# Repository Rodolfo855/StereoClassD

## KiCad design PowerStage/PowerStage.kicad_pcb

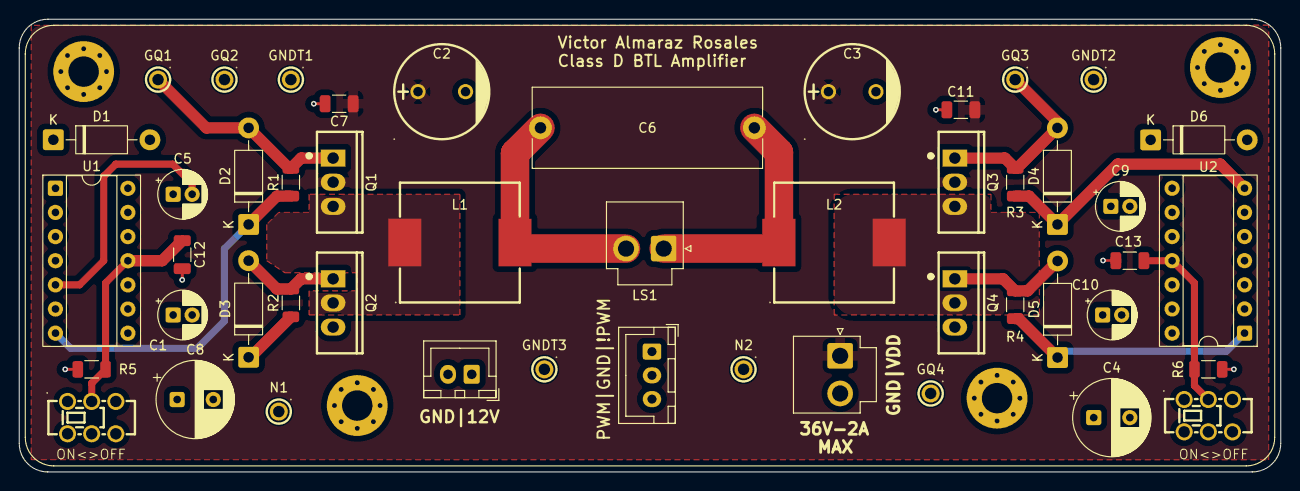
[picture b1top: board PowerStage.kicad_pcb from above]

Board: 4 copper layers, 132.7 x 47.6 mm, 52 parts (0 on the bottom side), 21 nets.

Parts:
C1, C5: C_Polarized_Small; CP_Radial_D5.0mm_P2.00mm
C2, C3: 470uF 16V; C46550425_CAP-TH_BD10_0-P5_00-D0_6-FD-A
C4, C8: 100uF; CP_Radial_D8.0mm_P3.80mm
C6: 680nF; C_Rect_L24.0mm_W8.3mm_P22.50mm_MKT
C7, C11: 100nF; C_1206_3216Metric
C9, C10: 1uF; CP_Radial_D5.0mm_P2.00mm
C12: 100nF 1206; C_1206_3216Metric
C13: 100nF-1206; C_1206_3216Metric
D1, D2, D3, D4, D5, D6: 1N5819; D_DO-41_SOD81_P10.16mm_Horizontal
GNDT1, GNDT2, GNDT3: TestPoint; C5277086_TEST-TH_BD2_54-P1_4_RED
GQ1, GQ2, GQ3, GQ4: TestPoint; C5277086_TEST-TH_BD2_54-P1_4_RED
H1, H2, H3, H4: MountingHole; MountingHole_3.2mm_M3_Pad_Via
J1: Conn_01x02; JST_VH_B2P-VH_1x02_P3.96mm_Vertical
J2: Conn_01x02; JST_XH_B2B-XH-A_1x02_P2.50mm_Vertical
J3: Conn_01x03; JST_XH_B3B-XH-A_1x03_P2.50mm_Vertical
L1, L2: MDA1365-470M; C2847587_IND-SMD_L13_5-W12_6_TMPA1265SP-100MN-D
LS1: 8 Ohms; JST_VH_B2P-VH_1x02_P3.96mm_Vertical
N1, N2: TestPoint; C5277086_TEST-TH_BD2_54-P1_4_RED
Q1, Q2, Q3, Q4: IRFB4227PBF; C2652_TO-220-3_L10_0-W4_5-P2_54-L
R1: R_Small_US; R_1206_3216Metric
R2, R3, R4: 10; R_1206_3216Metric
R5, R6: 10k-1206; R_1206_3216Metric
SW1, SW2: K2-2235D-F1; C108742_SW-TH_K2-2235D-F1
U1, U2: IR2110; DIP-14_W7.62mm_Socket

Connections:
!PWM: J3.1, U1.12 (LIN), U2.10 (HIN)
+12V: C1.1, C4.1, C8.1, C10.1, D1.2 (A), D6.2 (A), J2.1, SW1.1, SW2.1, U1.3 (VCC), U1.9 (VDD), U2.3 (VCC), U2.9 (VDD)
GND: C1.2, C2.2, C3.2, C4.2, C7.2, C8.2, C10.2, C11.2, C12.2, C13.2, GNDT1.1, GNDT2.1, GNDT3.1, J1.2, J2.2, J3.2, Q2.3 (S), Q4.3 (S), R5.2, R6.2, SW1.3, SW2.3, U1.2 (COM), U1.13 (VSS), U2.2 (COM), U2.13 (VSS)
unnamed: C6.1, L2.1, LS1.1
unnamed: C6.2, L1.2, LS1.2
unnamed: C5.1, D1.1 (K), U1.6 (VB)
unnamed: D2.2 (A), GQ1.1, Q1.1 (G), R1.2
unnamed: D2.1 (K), R1.1, U1.7 (HO)
unnamed: D3.2 (A), GQ2.1, Q2.1 (G), R2.2
unnamed: D3.1 (K), R2.1, U1.1 (LO)
unnamed: D4.2 (A), GQ3.1, Q3.1 (G), R3.1
unnamed: D4.1 (K), R3.2, U2.7 (HO)
unnamed: D5.2 (A), GQ4.1, Q4.1 (G), R4.1
unnamed: D5.1 (K), R4.2, U2.1 (LO)
unnamed: C9.1, D6.1 (K), U2.6 (VB)
unnamed: C5.2, L1.1, N1.1, Q1.3 (S), Q2.2 (D), U1.5 (VS)
unnamed: C9.2, L2.2, N2.1, Q3.3 (S), Q4.2 (D), U2.5 (VS)
unnamed: C12.1, R5.1, SW1.2, U1.11 (SD)
unnamed: C13.1, R6.1, SW2.2, U2.11 (SD)
PWM: J3.3, U1.10 (HIN), U2.12 (LIN)
VDC: C2.1, C3.1, C7.1, C11.1, J1.1, Q1.2 (D), Q3.2 (D)

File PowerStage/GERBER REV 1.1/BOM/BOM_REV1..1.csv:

"Reference","Value","DNP","Exclude from BOM","Footprint","LCSC"
"C1","C_Polarized_Small","","","Capacitor_THT:CP_Radial_D5.0mm_P2.00mm","C330941"
"C2","470uF 16V","","","lcsc_footprints:C46550425_CAP-TH_BD10_0-P5_00-D0_6-FD-A","C2837182"
"C3","470uF 16V","","","lcsc_footprints:C46550425_CAP-TH_BD10_0-P5_00-D0_6-FD-A","C2837182"
"C4","100uF","","","Capacitor_THT:CP_Radial_D8.0mm_P3.50mm","C1669449"
"C5","C_Polarized_Small","","","Capacitor_THT:CP_Radial_D5.0mm_P2.00mm","C330941"
"C6","680nF","","Excluded from BOM","Capacitor_THT:C_Rect_L24.0mm_W8.3mm_P22.50mm_MKT",""
"C7","100nF","","","Capacitor_SMD:C_1206_3216Metric","C24497"
"C8","100uF","","","Capacitor_THT:CP_Radial_D8.0mm_P3.50mm","C1669449"
"C9","1uF","","","Capacitor_THT:CP_Radial_D5.0mm_P2.00mm","C330941"
"C10","1uF","","","Capacitor_THT:CP_Radial_D5.0mm_P2.00mm","C330941"
"C11","100nF","","","Capacitor_SMD:C_1206_3216Metric","C24497"
"C12","100nF 1206","","","Capacitor_SMD:C_1206_3216Metric","C24497"
"C13","100nF-1206","","","Capacitor_SMD:C_1206_3216Metric","C24497"
"D1","1N5819","","","Diode_THT:D_DO-41_SOD81_P10.16mm_Horizontal","C16588"
"D2","1N5819","","","Diode_THT:D_DO-41_SOD81_P10.16mm_Horizontal","C16588"
"D3","1N5819","","","Diode_THT:D_DO-41_SOD81_P10.16mm_Horizontal","C16588"
"D4","1N5819","","","Diode_THT:D_DO-41_SOD81_P10.16mm_Horizontal","C16588"
"D5","1N5819","","","Diode_THT:D_DO-41_SOD81_P10.16mm_Horizontal","C16588"
"D6","1N5819","","","Diode_THT:D_DO-41_SOD81_P10.16mm_Horizontal","C16588"
"H1","MountingHole","","Excluded from BOM","MountingHole:MountingHole_3.2mm_M3_Pad_Via",""
"H2","MountingHole","","Excluded from BOM","MountingHole:MountingHole_3.2mm_M3_Pad_Via",""
"H3","MountingHole","","Excluded from BOM","MountingHole:MountingHole_3.2mm_M3_Pad_Via",""
"H4","MountingHole","","Excluded from BOM","MountingHole:MountingHole_3.2mm_M3_Pad_Via",""
"J1","Conn_01x02","","Excluded from BOM","Connector_JST:JST_VH_B2P-VH_1x02_P3.96mm_Vertical",""
"J2","Conn_01x02","","Excluded from BOM","Connector_JST:JST_XH_B2B-XH-A_1x02_P2.50mm_Vertical",""
"J3","Conn_01x03","","Excluded from BOM","Connector_JST:JST_XH_B3B-XH-A_1x03_P2.50mm_Vertical",""
"L1","MDA1365-470M","","","lcsc_footprints:C2847587_IND-SMD_L13_5-W12_6_TMPA1265SP-100MN-D","C2847587"
"L2","MDA1365-470M","","","lcsc_footprints:C2847587_IND-SMD_L13_5-W12_6_TMPA1265SP-100MN-D","C2847587"
"LS1","8 Ohms","","Excluded from BOM","Connector_JST:JST_VH_B2P-VH_1x02_P3.96mm_Vertical",""
"Q1","IRFB4227PBF","","","lcsc_footprints:C2652_TO-220-3_L10_0-W4_5-P2_54-L","C2652"
"Q2","IRFB4227PBF","","","lcsc_footprints:C2652_TO-220-3_L10_0-W4_5-P2_54-L","C2652"
"Q3","IRFB4227PBF","","","lcsc_footprints:C2652_TO-220-3_L10_0-W4_5-P2_54-L","C2652"
"Q4","IRFB4227PBF","","","lcsc_footprints:C2652_TO-220-3_L10_0-W4_5-P2_54-L","C2652"
"R1","R_Small_US","","","Resistor_SMD:R_1206_3216Metric","C17903"
"R2","10","","","Resistor_SMD:R_1206_3216Metric","C17903"
"R3","10","","","Resistor_SMD:R_1206_3216Metric","C17903"
"R4","10","","","Resistor_SMD:R_1206_3216Metric","C17903"
"R5","10k-1206","","","Resistor_SMD:R_1206_3216Metric","C17902"
"R6","10k-1206","","","Resistor_SMD:R_1206_3216Metric","C17902"
"SW1","K2-2235D-F1","","","lcsc_footprints:C108742_SW-TH_K2-2235D-F1","C108742"
"SW2","K2-2235D-F1","","","lcsc_footprints:C108742_SW-TH_K2-2235D-F1","C108742"
"TP1","TestPoint","","","lcsc_footprints:C5277086_TEST-TH_BD2_54-P1_4_RED","C5277086"
"TP2","TestPoint","","","lcsc_footprints:C5277086_TEST-TH_BD2_54-P1_4_RED","C5277086"
"TP3","TestPoint","","","lcsc_footprints:C5277086_TEST-TH_BD2_54-P1_4_RED","C5277086"
"TP4","TestPoint","","","lcsc_footprints:C5277086_TEST-TH_BD2_54-P1_4_RED","C5277086"
"TP5","TestPoint","","","lcsc_footprints:C5277086_TEST-TH_BD2_54-P1_4_RED","C5277086"
"TP6","TestPoint","","","lcsc_footprints:C5277086_TEST-TH_BD2_54-P1_4_RED","C5277086"
"TP7","TestPoint","","","lcsc_footprints:C5277086_TEST-TH_BD2_54-P1_4_RED","C5277086"
"TP8","TestPoint","","","lcsc_footprints:C5277086_TEST-TH_BD2_54-P1_4_RED","C5277086"
"TP9","TestPoint","","","lcsc_footprints:C5277086_TEST-TH_BD2_54-P1_4_RED","C5277086"
"U1","IR2110","","Excluded from BOM","Package_DIP:DIP-14_W7.62mm_Socket",""
"U2","IR2110","","Excluded from BOM","Package_DIP:DIP-14_W7.62mm_Socket",""

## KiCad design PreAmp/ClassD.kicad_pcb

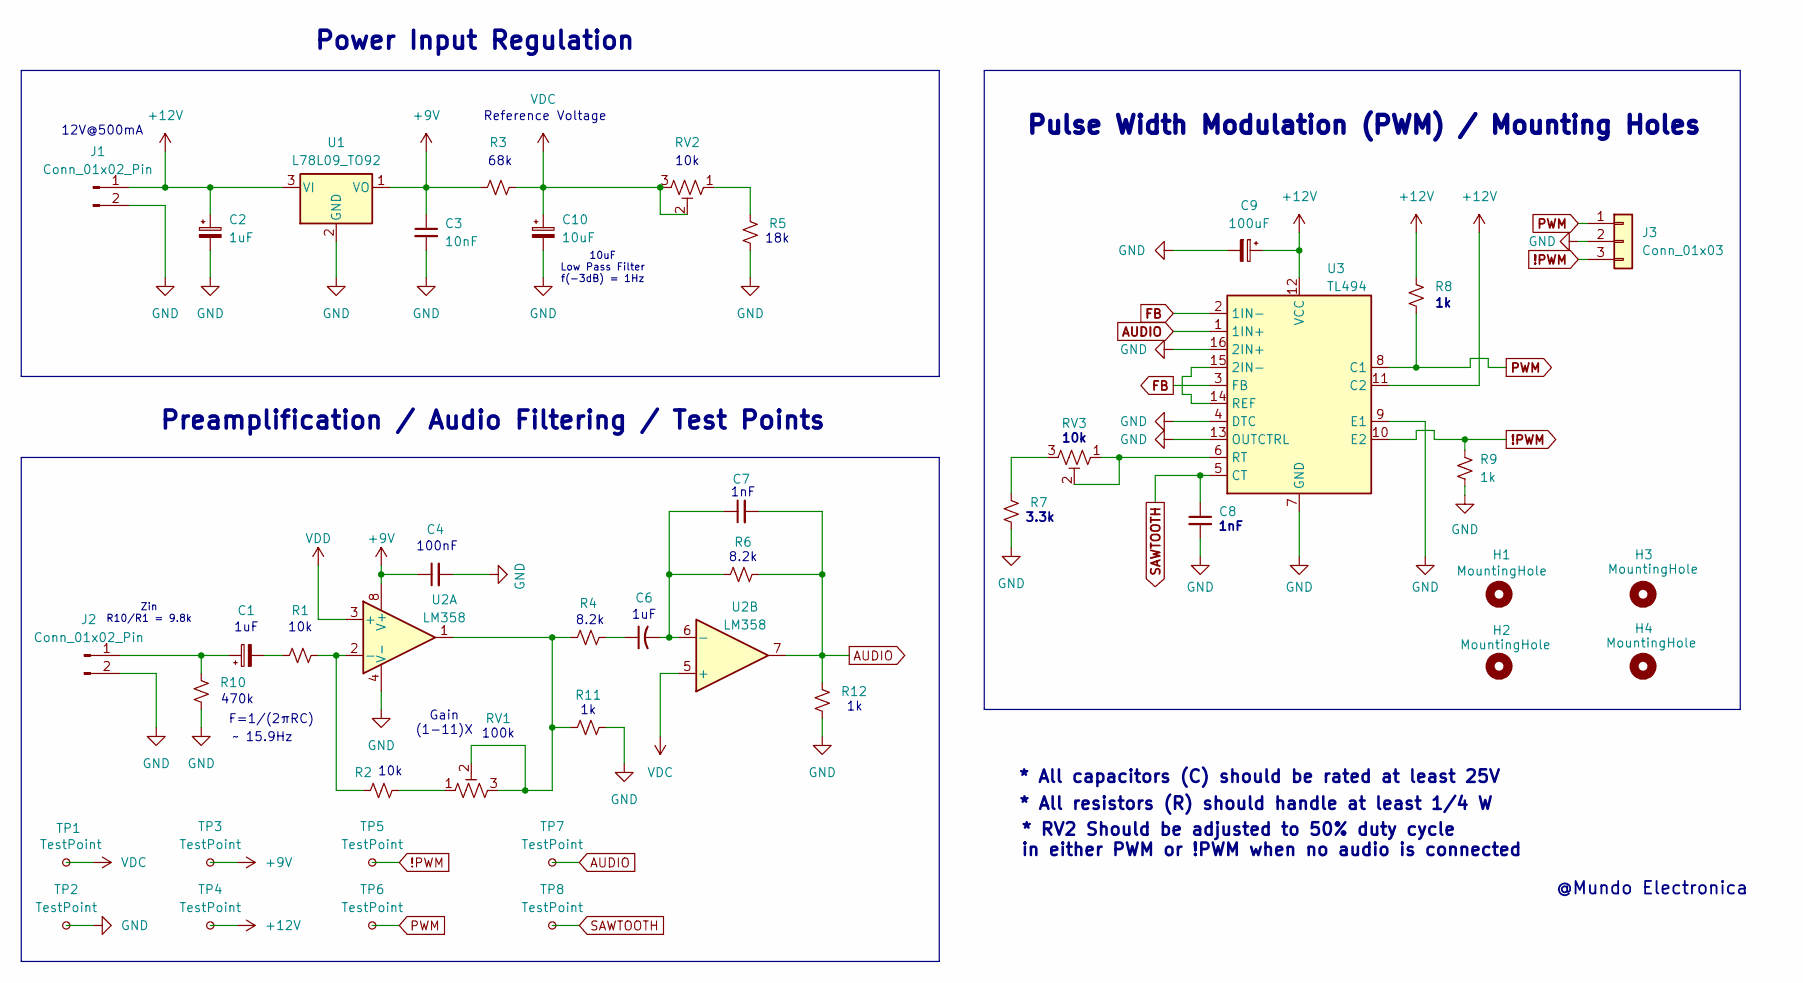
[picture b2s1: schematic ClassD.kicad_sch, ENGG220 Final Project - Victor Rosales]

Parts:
C1: C_Polarized_Small; CP_Radial_D5.0mm_P2.00mm
C2: 1uF; CP_Radial_D5.0mm_P2.00mm
C3: 10nF; C_Disc_D3.8mm_W2.6mm_P2.50mm
C4: C_Small; C_Disc_D5.0mm_W2.5mm_P5.00mm
C6: C_Small_US; CP_Radial_D5.0mm_P2.00mm
C7, C8: C_Small; C_Disc_D3.8mm_W2.6mm_P2.50mm
C9: 100uF; CP_Radial_D8.0mm_P3.50mm
C10: 10uF; CP_Radial_D5.0mm_P2.00mm
H1, H2, H3, H4: MountingHole; MountingHole_3.2mm_M3_Pad_Via
J1: Conn_01x02_Pin; BarrelJack_GCT_DCJ200-10-A_Horizontal
J2: Conn_01x02_Pin; JST_XH_B2B-XH-A_1x02_P2.50mm_Vertical
J3: Conn_01x03; JST_XH_B3B-XH-A_1x03_P2.50mm_Vertical
R1, R2, R3, R4, R5, R6, R7, R8, R10, R11, R12: R_Small_US; R_Axial_DIN0204_L3.6mm_D1.6mm_P7.62mm_Horizontal
R9: 1k
RV1, RV2, RV3: R_Potentiometer_Trim_US; Potentiometer_Bourns_3296W_Vertical
TP1, TP2, TP3, TP4, TP5, TP6, TP7, TP8: TestPoint; TestPoint_THTPad_D2.0mm_Drill1.0mm
U1: L78L09_TO92; TO-92_Inline_Wide
U2: LM358; DIP-8_W7.62mm_Socket
U3: TL494; DIP-18_W7.62mm_Socket

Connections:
!PWM: J3.3, R9.1, TP5.1, U3.10 (E2)
+9V: C3.1, C4.1, R3.1, TP3.1, U1.1 (VO), U2.8 (V+)
+12V: C2.1, C9.1, J1.1, R8.1, TP4.1, U1.3 (VI), U3.11 (C2), U3.12 (VCC)
AUDIO: C7.2, R6.2, R12.1, TP7.1, U2.7, U3.1 (1IN+)
FB: U3.2 (1IN-), U3.3 (FB)
GND: C2.2, C3.2, C4.2, C8.2, C9.2, C10.2, J1.2, J2.2, J3.2, R5.2, R7.2, R9.2, R10.2, R11.2, R12.2, TP2.1, U1.2 (GND), U2.4 (V-), U3.4 (DTC), U3.7 (GND), U3.9 (E1), U3.13 (OUTCTRL), U3.16 (2IN+)
unnamed: C1.2, R1.1
unnamed: C6.1, R4.2
unnamed: C1.1, J2.1, R10.1
unnamed: R2.2, RV1.1
unnamed: R5.1, RV2.1
unnamed: R7.1, RV3.3
unnamed: R4.1, R11.1, RV1.2, RV1.3, U2.1
unnamed: R1.2, R2.1, U2.2 (-)
unnamed: C6.2, C7.1, R6.1, U2.6 (-)
unnamed: U3.14 (REF), U3.15 (2IN-)
unnamed: RV3.1, RV3.2, U3.6 (RT)
PWM: J3.1, R8.2, TP6.1, U3.8 (C1)
SAWTOOTH: C8.1, TP8.1, U3.5 (CT)
VDC: C10.1, R3.2, RV2.2, RV2.3, TP1.1, U2.5 (+)
VDD: U2.3 (+)

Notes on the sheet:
Pulse Width Modulation (PWM) / Mounting Holes
3.3k
Power Input Regulation
1nF
* All capacitors (C) should be rated at least 25V
~ 15.9Hz
100k
Reference Voltage
470k
1uF
10k
10uF Low Pass Filter f(-3dB) = 1Hz
* All resistors (R) should handle at least 1/4 W
F=1/(2πRC)
@Mundo Electronica
68k
* RV2 Should be adjusted to 50% duty cycle in either PWM or !PWM when no audio is connected
Preamplification / Audio Filtering / Test Points
8.2k
12V@500mA
18k
Zin R10/R1 = 9.8k
Gain (1-11)X
100nF

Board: 2 copper layers, 41 parts (0 on the bottom side), 20 nets, no tracks yet.
